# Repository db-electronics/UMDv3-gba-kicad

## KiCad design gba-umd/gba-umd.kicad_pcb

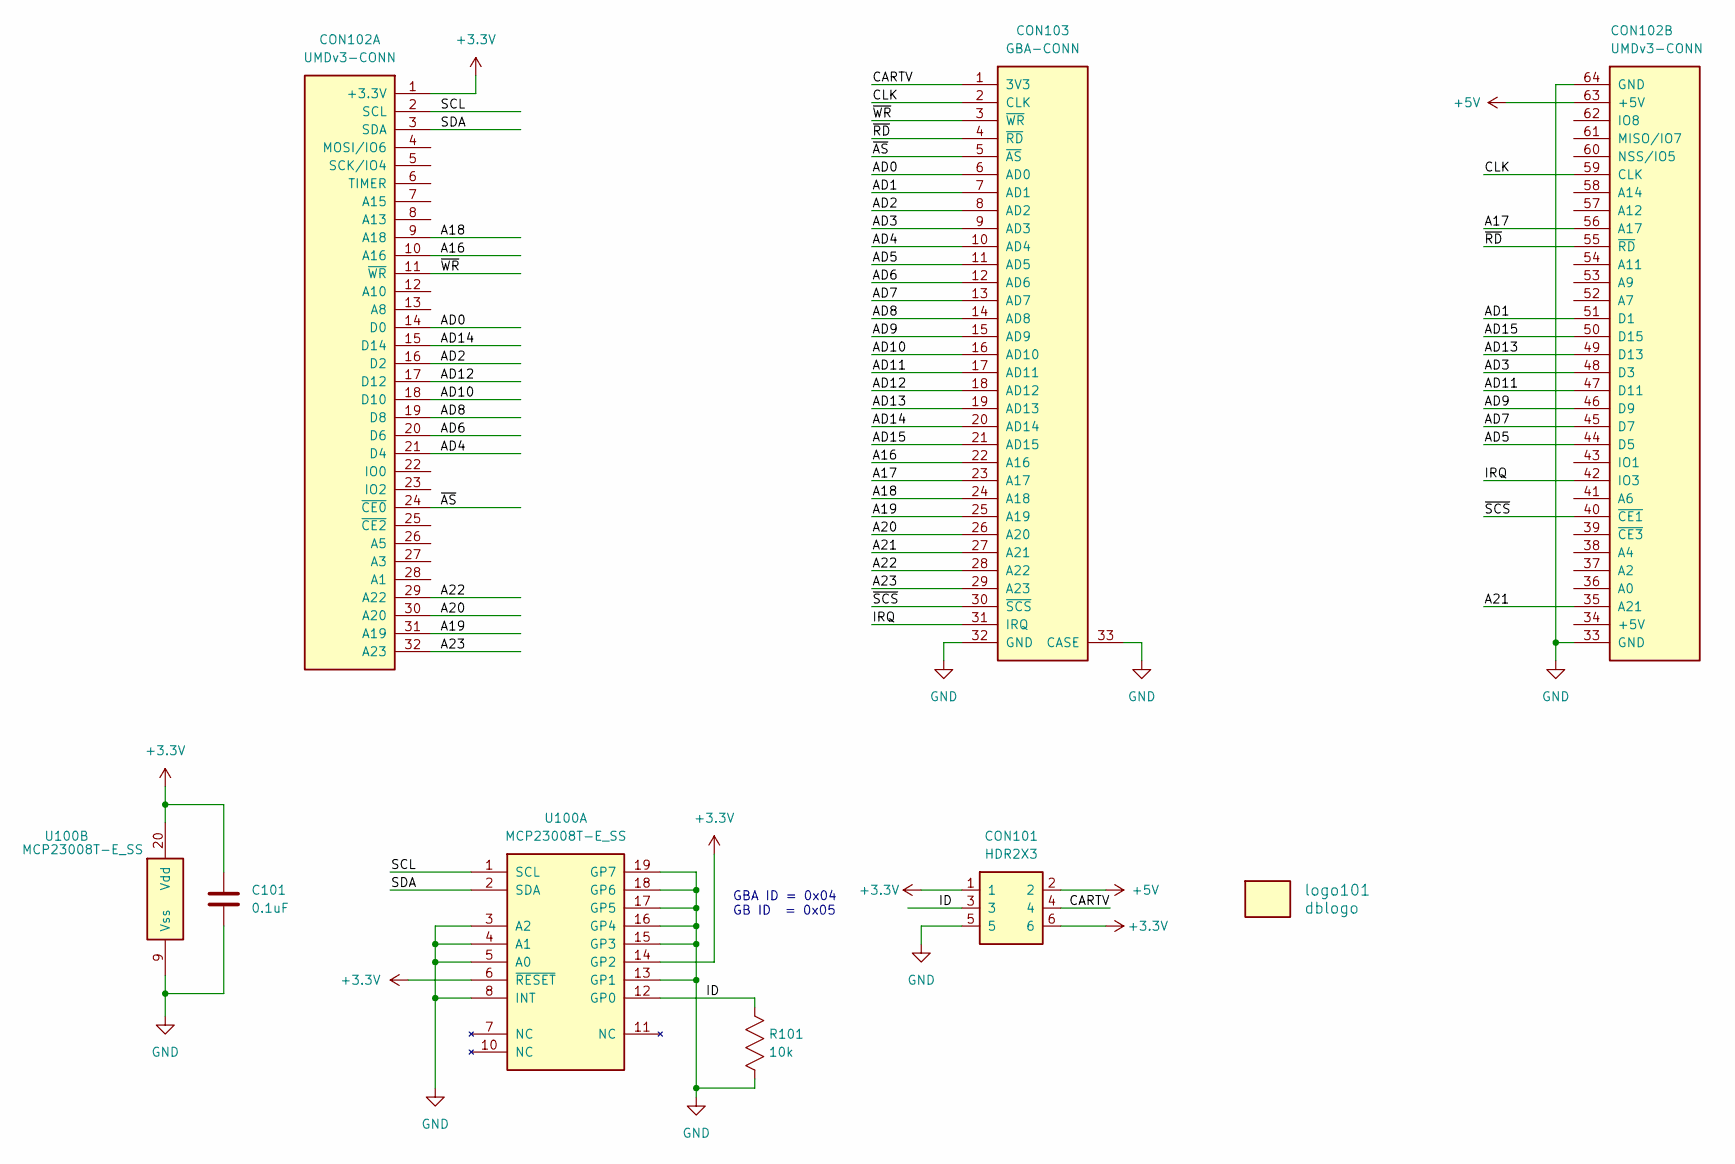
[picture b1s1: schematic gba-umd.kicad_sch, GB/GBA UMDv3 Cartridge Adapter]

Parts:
C101: 0.1uF; 0603; Digikey 1276-1935-1-ND
CON101: HDR2X3; Digikey 609-3234-ND
CON102: UMDv3-CONN; UMDv3-CONN-DIP64; Digikey SAM1211-32-ND
CON103: GBA-CONN; Digikey #ND
R101: 10k; 0603; Digikey 311-10.0KHRCT-ND
U100: MCP23008T-E_SS; SSOP-20; Digikey MCP23008T-E/SSCT-ND
logo101: dblogo; db-logo_7.5mm

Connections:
+3V3: C101.1, CON101.1, CON101.6, CON102.1 (+3.3V), U100.6 (~RESET), U100.14 (GP2), U100.20 (Vdd)
+5V: CON101.2, CON102.63 (+5V)
/A16: CON102.10 (A16), CON103.22 (A16)
/A17: CON102.56 (A17), CON103.23 (A17)
/A18: CON102.9 (A18), CON103.24 (A18)
/A19: CON102.31 (A19), CON103.25 (A19)
/A20: CON102.30 (A20), CON103.26 (A20)
/A21: CON102.35 (A21), CON103.27 (A21)
/A22: CON102.29 (A22), CON103.28 (A22)
/A23: CON102.32 (A23), CON103.29 (A23)
/AD0: CON102.14 (D0), CON103.6 (AD0)
/AD1: CON102.51 (D1), CON103.7 (AD1)
/AD2: CON102.16 (D2), CON103.8 (AD2)
/AD3: CON102.48 (D3), CON103.9 (AD3)
/AD4: CON102.21 (D4), CON103.10 (AD4)
/AD5: CON102.44 (D5), CON103.11 (AD5)
/AD6: CON102.20 (D6), CON103.12 (AD6)
/AD7: CON102.45 (D7), CON103.13 (AD7)
/AD8: CON102.19 (D8), CON103.14 (AD8)
/AD9: CON102.46 (D9), CON103.15 (AD9)
/AD10: CON102.18 (D10), CON103.16 (AD10)
/AD11: CON102.47 (D11), CON103.17 (AD11)
/AD12: CON102.17 (D12), CON103.18 (AD12)
/AD13: CON102.49 (D13), CON103.19 (AD13)
/AD14: CON102.15 (D14), CON103.20 (AD14)
/AD15: CON102.50 (D15), CON103.21 (AD15)
/CARTV: CON101.4, CON103.1 (3V3)
/CLK: CON102.59 (CLK), CON103.2 (CLK)
/ID: CON101.3, R101.1, U100.12 (GP0)
/IRQ: CON102.42 (IO3), CON103.31 (IRQ)
/SCL: CON102.2 (SCL), U100.1 (SCL)
/SDA: CON102.3 (SDA), U100.2 (SDA)
/~AS: CON102.24 (~CE0), CON103.5 (~AS)
/~RD: CON102.55 (~RD), CON103.4 (~RD)
/~SCS: CON102.40 (~CE1), CON103.30 (~SCS)
/~WR: CON102.11 (~WR), CON103.3 (~WR)
GND: C101.2, CON101.5, CON102.33 (GND), CON102.64 (GND), CON103.32 (GND), CON103.33 (CASE), R101.2, U100.3 (A2), U100.4 (A1), U100.5 (A0), U100.8 (INT), U100.9 (Vss), U100.13 (GP1), U100.15 (GP3), U100.16 (GP4), U100.17 (GP5), U100.18 (GP6), U100.19 (GP7)

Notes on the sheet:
GBA ID = 0x04 GB ID = 0x05

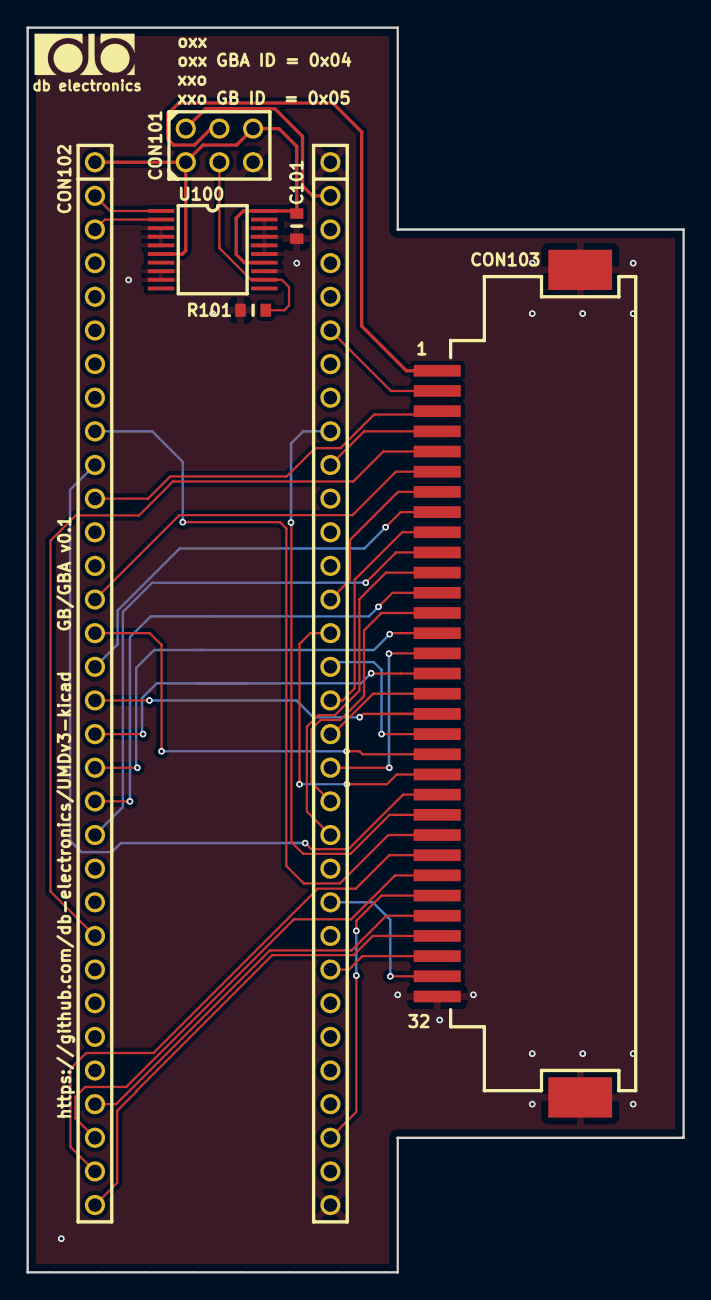
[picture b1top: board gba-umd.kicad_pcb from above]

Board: 2 copper layers, 49.5 x 94.0 mm, 7 parts (0 on the bottom side), 37 nets.

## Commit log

2023-12-16 initial files commit
2023-12-17 work
2023-12-17 schematic done
2023-12-18 prelim pcb routing
2023-12-20 version 0.1

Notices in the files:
gba-umd/gba-umd.kicad_sch:
Licensed under CERN OHL v1.2
Copyright René Richard 2023
